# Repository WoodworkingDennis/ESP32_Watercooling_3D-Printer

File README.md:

<h1>ESP32_Watercooling_3D-Printer</h1>
<p>
</br>Ansteuerung von drei unabhängingen PWM-Geräten
</br>Auslesen von sechs verschiedenen PT100 Widerständen
</br>Anzeige und Einstellungen über LCD-Display
</br>ESP32 auf Custom PCB
</p>

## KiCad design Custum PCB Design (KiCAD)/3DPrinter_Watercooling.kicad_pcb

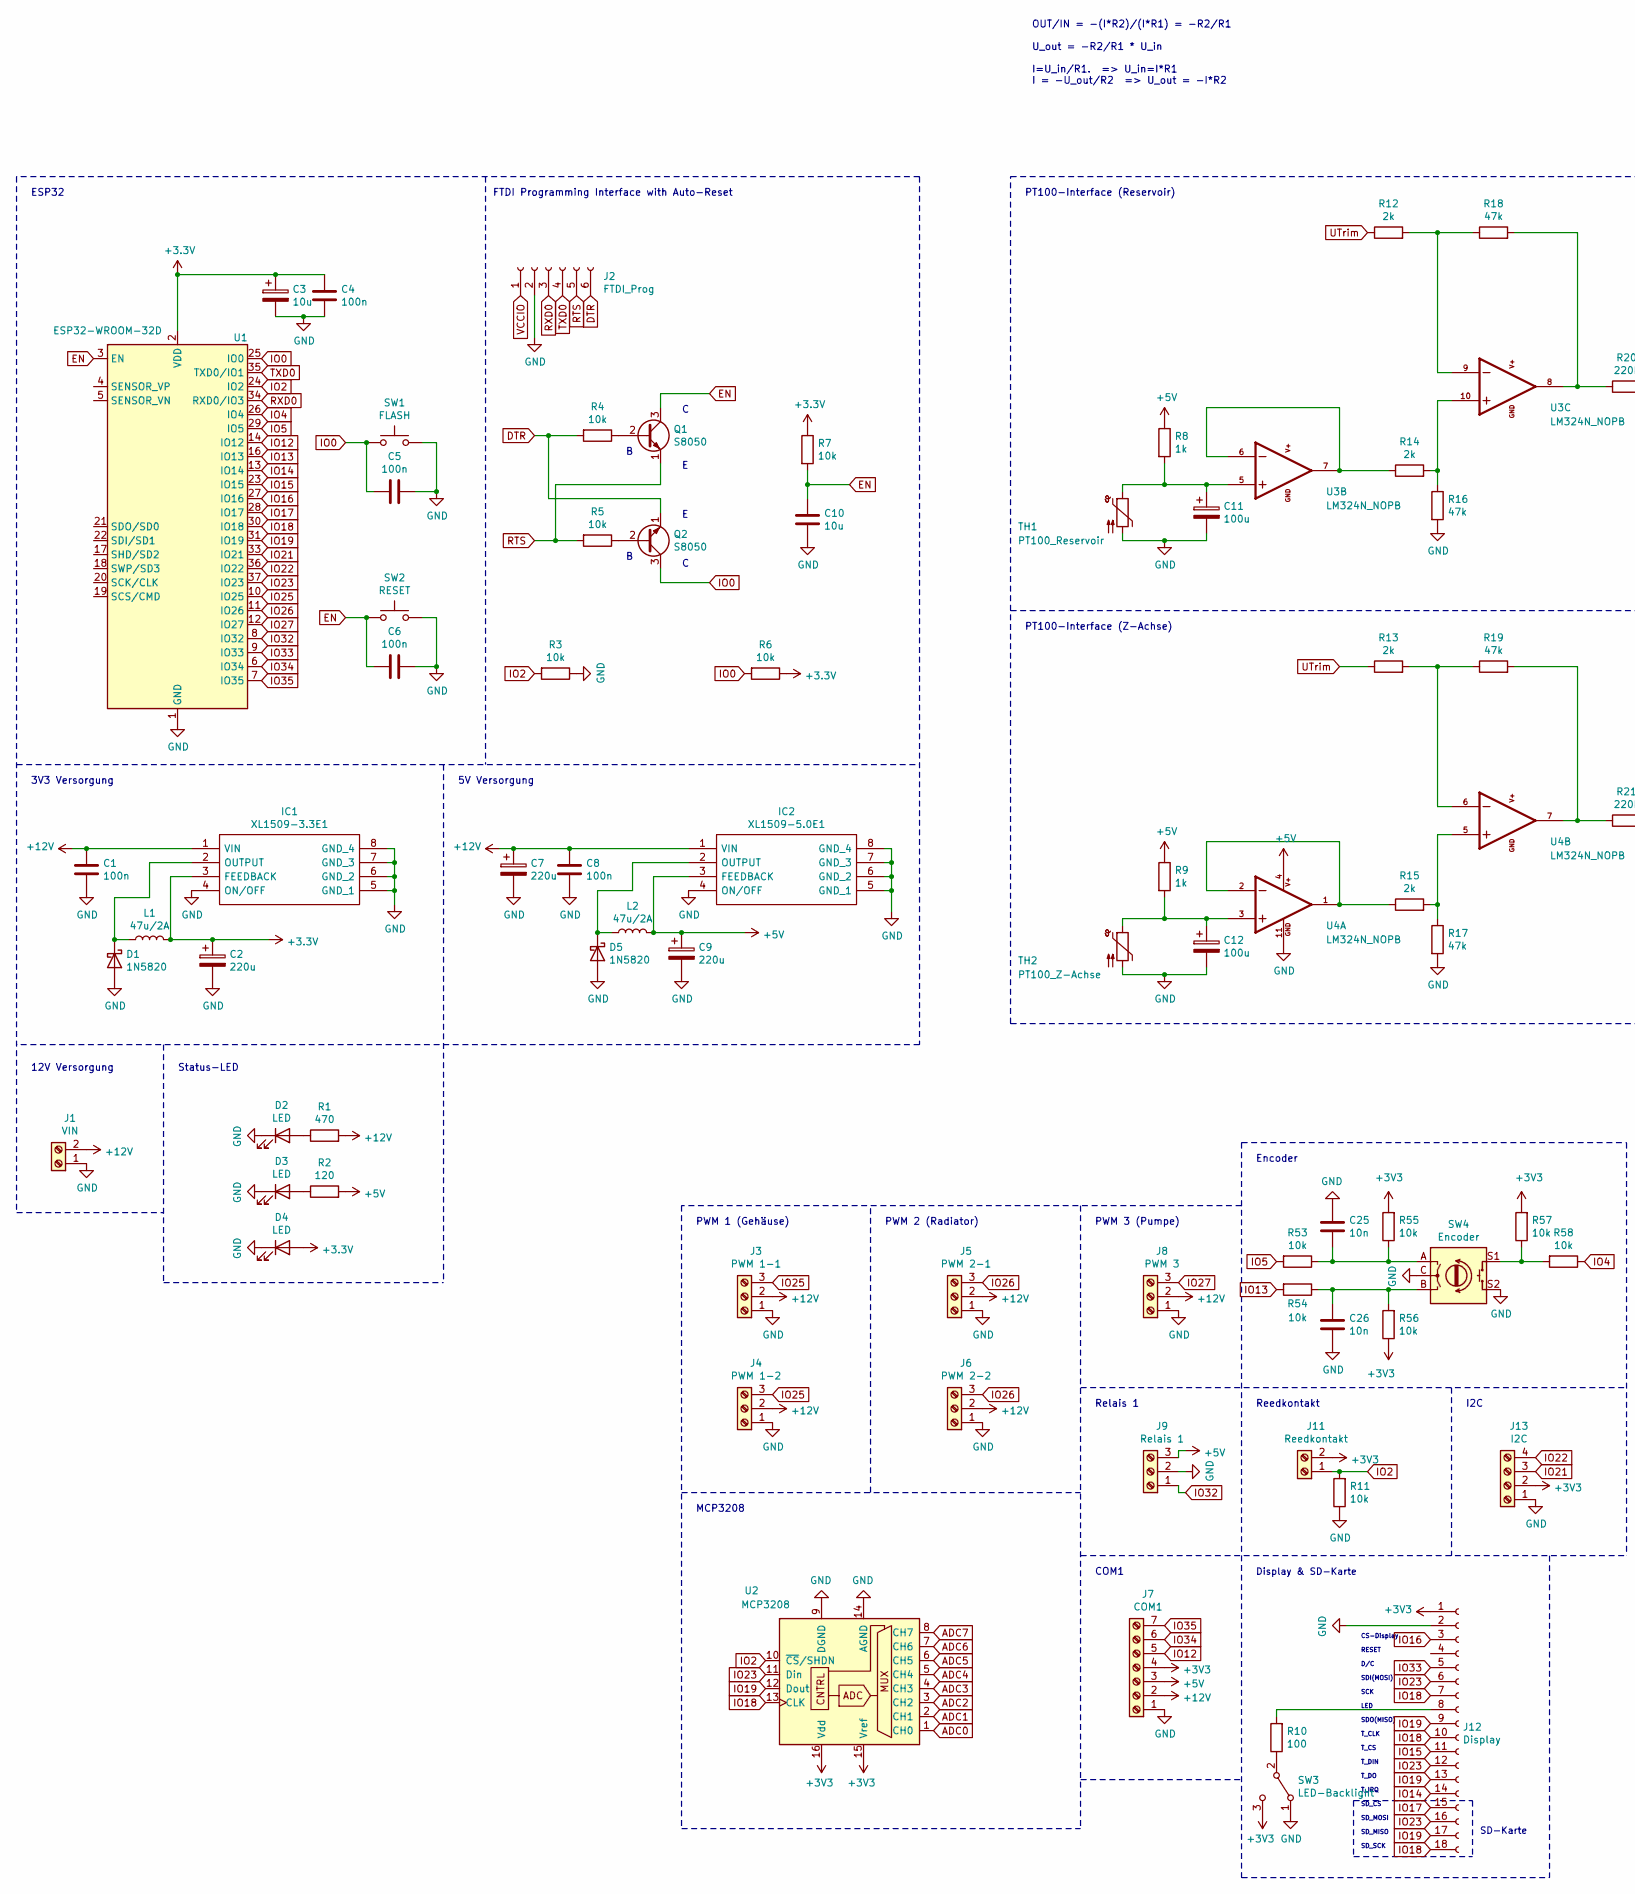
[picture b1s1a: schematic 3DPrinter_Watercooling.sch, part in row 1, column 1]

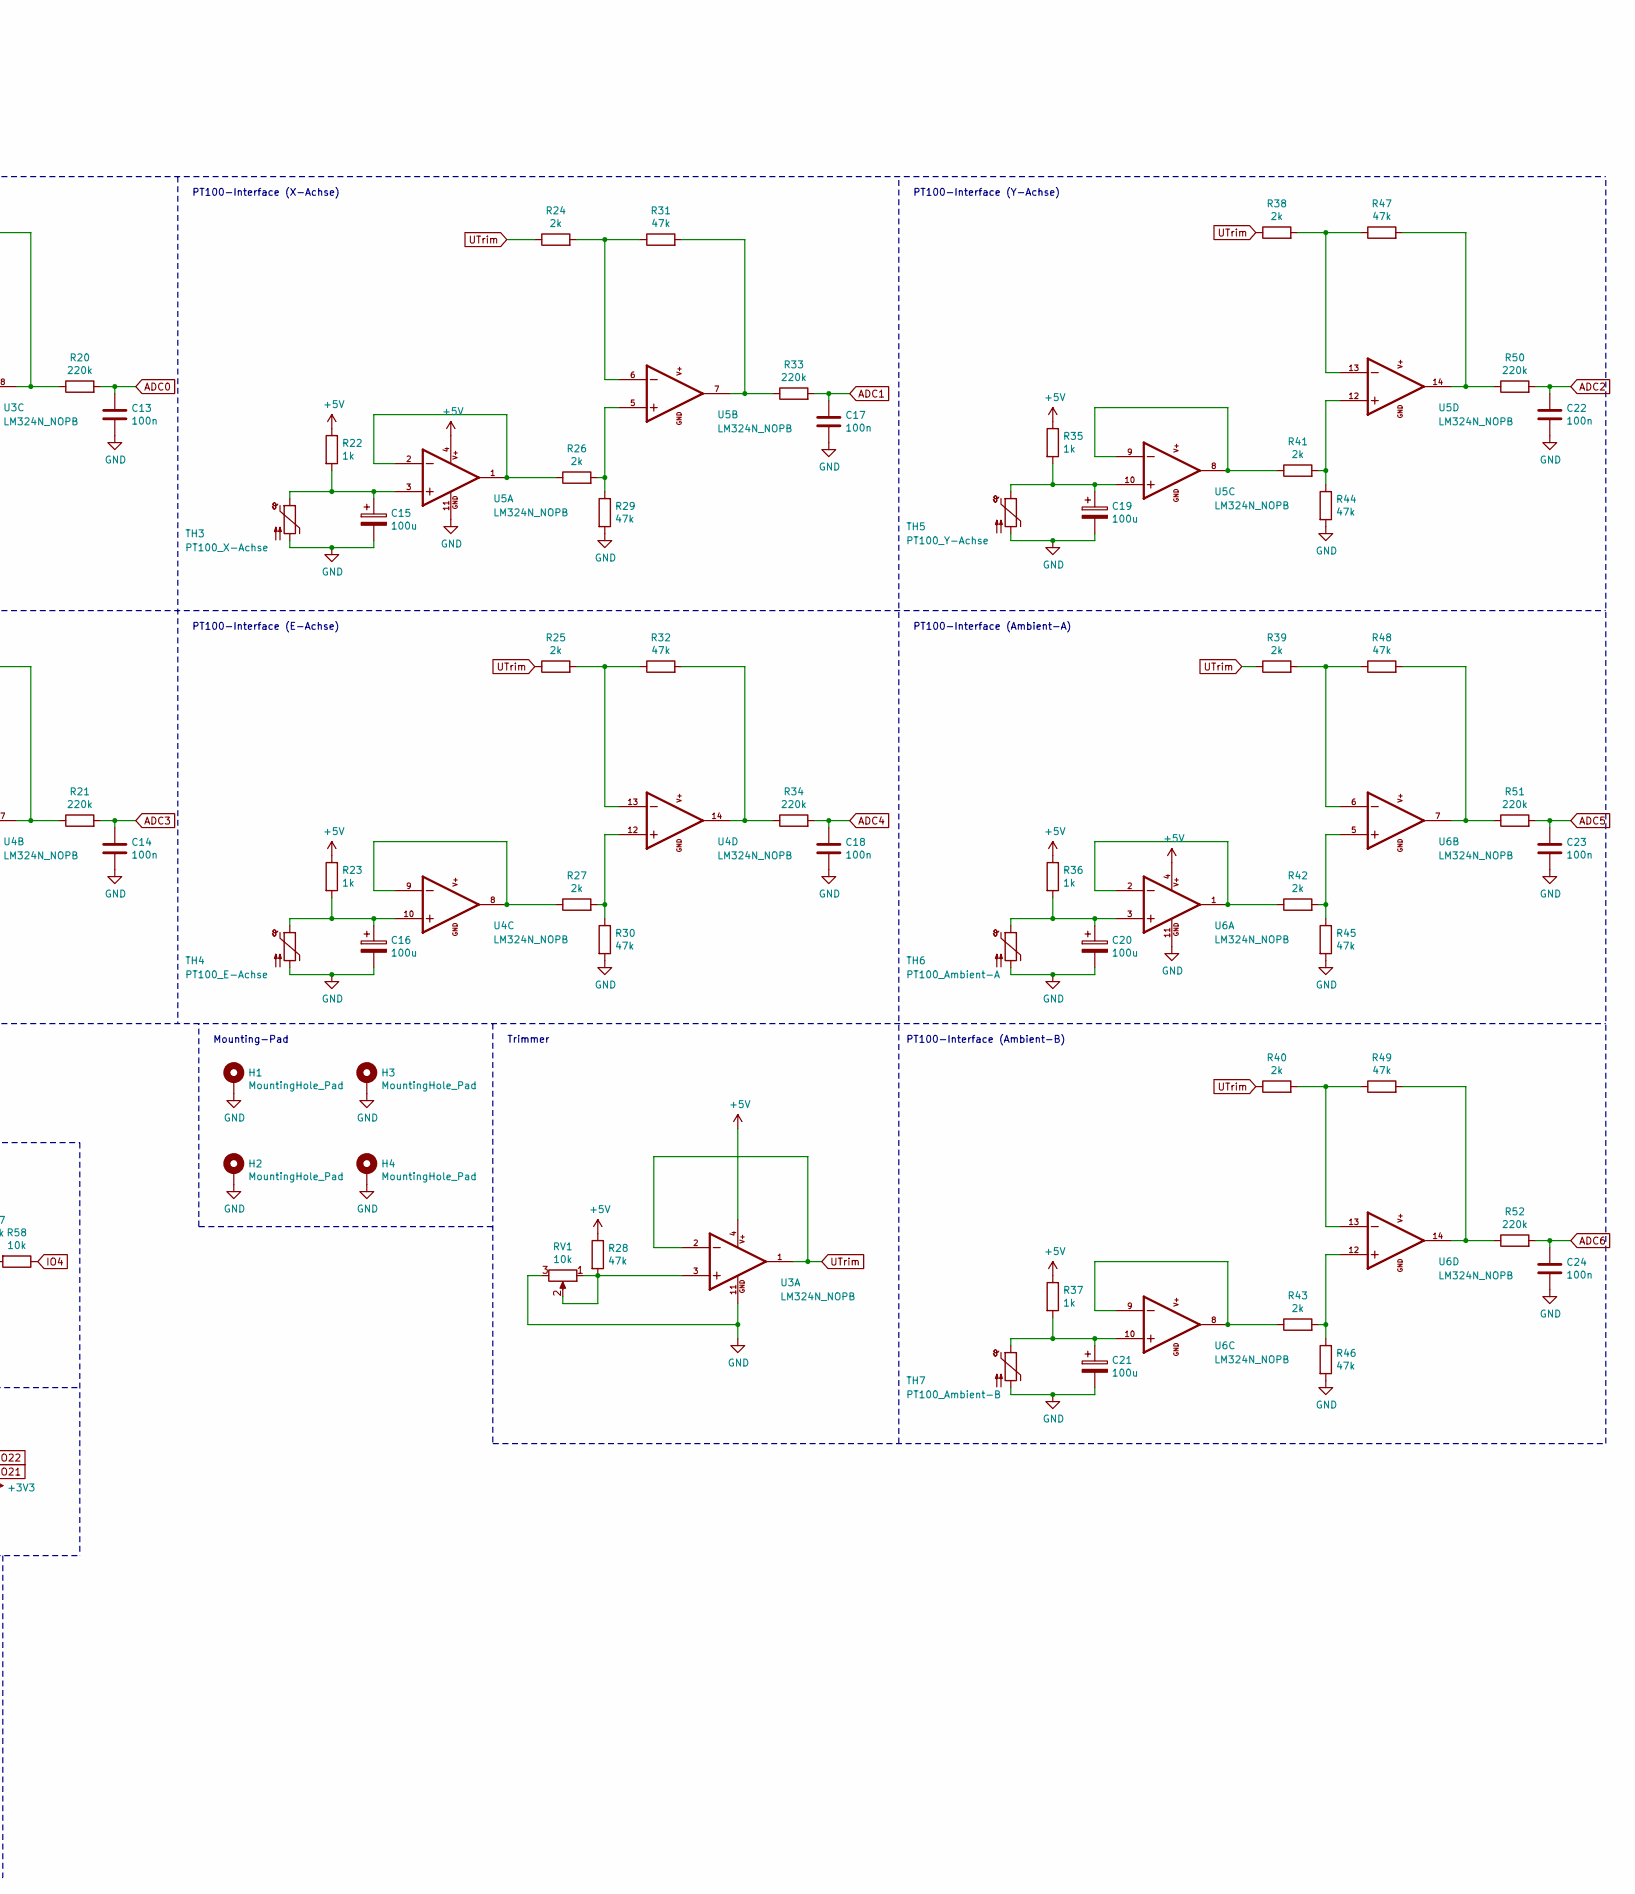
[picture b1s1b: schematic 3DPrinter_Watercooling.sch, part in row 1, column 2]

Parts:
C1, C4, C5, C6, C8, C13, C14, C17, C18, C22, C23, C24: 100n; C_0805_2012Metric_Pad1.18x1.45mm_HandSolder
C2, C7, C9: 220u; CP_Radial_D6.3mm_P2.50mm
C3: 10u; CP_Radial_D4.0mm_P1.50mm
C10: 10u; C_0805_2012Metric_Pad1.18x1.45mm_HandSolder
C11, C12, C15, C16, C19, C20, C21: 100u; CP_Radial_D5.0mm_P2.00mm
C25, C26: 10n; C_0805_2012Metric_Pad1.18x1.45mm_HandSolder
D1, D5: 1N5820; D_DO-201AD_P15.24mm_Horizontal
D2, D3, D4: LED; LED_0805_2012Metric_Pad1.15x1.40mm_HandSolder
H1, H2, H3, H4: MountingHole_Pad; MountingHole_2.2mm_M2_Pad_Via
IC1: XL1509-3.3E1; SOIC127P600X175-8N; Manufacturer_Part_Number XL1509-3.3E1
IC2: XL1509-5.0E1; SOIC127P600X175-8N; Manufacturer_Part_Number XL1509-5.0E1
J1: VIN; WJ301V-5.0-2P
J2: FTDI_Prog; PinHeader_1x06_P2.54mm_Vertical
J3: PWM 1-1; TE_282834-3
J4: PWM 1-2; TE_282834-3
J5: PWM 2-1; TE_282834-3
J6: PWM 2-2; TE_282834-3
J7: COM1; TE_282834-7
J8: PWM 3; TE_282834-3
J9: Relais 1; TE_282834-3
J11: Reedkontakt; TE_282834-2
J12: Display; 3.2 inch 320 240 SPI Serial TFT LCD Module
J13: I2C; TE_282834-4
L1, L2: 47u/2A; L_Radial_D10.0mm_P5.00mm_Fastron_07M
Q1, Q2: S8050; TO-92_Inline
R1: 470; R_Axial_DIN0207_L6.3mm_D2.5mm_P7.62mm_Horizontal
R2: 120; R_Axial_DIN0207_L6.3mm_D2.5mm_P7.62mm_Horizontal
R3, R4, R5, R6, R7, R11, R53, R54, R55, R56, R57, R58: 10k; R_Axial_DIN0207_L6.3mm_D2.5mm_P7.62mm_Horizontal
R8, R9, R22, R23, R35, R36, R37: 1k; R_Axial_DIN0207_L6.3mm_D2.5mm_P7.62mm_Horizontal
R10: 100; R_Axial_DIN0207_L6.3mm_D2.5mm_P7.62mm_Horizontal
R12, R13, R14, R15, R24, R25, R26, R27, R38, R39, R40, R41, R42, R43: 2k; R_Axial_DIN0207_L6.3mm_D2.5mm_P7.62mm_Horizontal
R16, R17, R18, R19, R28, R29, R30, R31, R32, R44, R45, R46, R47, R48, R49: 47k; R_Axial_DIN0207_L6.3mm_D2.5mm_P7.62mm_Horizontal
R20, R21, R33, R34, R50, R51, R52: 220k; R_Axial_DIN0207_L6.3mm_D2.5mm_P7.62mm_Horizontal
RV1: 10k; Potentiometer_Bourns_3296W_Vertical
SW1: FLASH; TS-1187A-B-A-B
SW2: RESET; TS-1187A-B-A-B
SW3: LED-Backlight; SW_Slide_1P2T_CK_OS102011MS2Q
SW4: Encoder; RotaryEncoder_Alps_EC11E-Switch_Vertical_H20mm
TH1: PT100_Reservoir; TE_282834-2
TH2: PT100_Z-Achse; TE_282834-2
TH3: PT100_X-Achse; TE_282834-2
TH4: PT100_E-Achse; TE_282834-2
TH5: PT100_Y-Achse; TE_282834-2
TH6: PT100_Ambient-A; TE_282834-2
TH7: PT100_Ambient-B; TE_282834-2
U1: ESP32-WROOM-32D; ESP32-WROOM-32
U2: MCP3208; SOIC127P600X175-16N
U3, U4, U5, U6: LM324N_NOPB; SOIC-14_3.9x8.7mm_P1.27mm; PARTREV D

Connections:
+5V: C9.1, IC2.3 (FEEDBACK), J7.3, J9.3, L2.2, R2.2, R8.1, R9.1, R22.1, R23.1, R28.1, R35.1, R36.1, R37.1, U3.4, U4.4, U5.4, U6.4
+12V: C1.1, C7.1, C8.1, IC1.1 (VIN), IC2.1 (VIN), J1.2, J3.2, J4.2, J5.2, J6.2, J7.2, J8.2, R1.2
ADC0: C13.1, R20.2, U2.1 (CH0)
ADC1: C17.1, R33.2, U2.2 (CH1)
ADC2: C22.1, R50.2, U2.3 (CH2)
ADC3: C14.1, R21.2, U2.4 (CH3)
ADC4: C18.1, R34.2, U2.5 (CH4)
ADC5: C23.1, R51.2, U2.6 (CH5)
ADC6: C24.1, R52.2, U2.7 (CH6)
ADC7: U2.8 (CH7)
DTR: J2.6, Q2.1 (E), R4.2
EN: C6.2, C10.1, Q1.3 (C), R7.2, SW2.1, U1.3 (EN)
GND: C1.2, C2.2, C3.2, C4.2, C5.1, C6.1, C7.2, C8.2, C9.2, C10.2, C11.2, C12.2, C13.2, C14.2, C15.2, C16.2, C17.2, C18.2, C19.2, C20.2, C21.2, C22.2, C23.2, C24.2, C25.1, C26.2, D1.2 (A), D2.1 (K), D3.1 (K), D4.1 (K), D5.2 (A), H1.1, H2.1, H3.1, H4.1, IC1.4 (ON/OFF), IC1.5 (GND_1), IC1.6 (GND_2), IC1.7 (GND_3), IC1.8 (GND_4), IC2.4 (ON/OFF), IC2.5 (GND_1), IC2.6 (GND_2), IC2.7 (GND_3), IC2.8 (GND_4), J1.1, J2.2, J3.1, J4.1, J5.1, J6.1, J7.1, J8.1, J9.2, J12.2, J13.1, R3.1, R11.1, R16.2, R17.2, R29.2, R30.2, R44.2, R45.2, R46.2, RV1.3, SW1.2, SW2.2, SW3.1 (A), SW4.C, SW4.S2, TH1.2, TH2.2, TH3.2, TH4.2, TH5.2, TH6.2, TH7.2, U1.1 (GND), U1.15 (GND), U1.38 (GND), U1.39 (GND), U2.9 (DGND), U2.14 (AGND), U3.11, U4.11, U5.11, U6.11
IO0: C5.2, Q2.3 (C), R6.2, SW1.1, U1.25 (IO0)
IO2: J11.1, R3.2, R11.2, U1.24 (IO2), U2.10 (~CS~/SHDN)
IO4: R58.1, U1.26 (IO4)
IO5: R53.2, U1.29 (IO5)
IO12: J7.5, U1.14 (IO12)
IO13: R54.2, U1.16 (IO13)
IO14: J12.14, U1.13 (IO14)
IO15: J12.11, U1.23 (IO15)
IO16: J12.3, U1.27 (IO16)
IO17: J12.15, U1.28 (IO17)
IO18: J12.7, J12.10, J12.18, U1.30 (IO18), U2.13 (CLK)
IO19: J12.9, J12.13, J12.17, U1.31 (IO19), U2.12 (Dout)
IO21: J13.3, U1.33 (IO21)
IO22: J13.4, U1.36 (IO22)
IO23: J12.6, J12.12, J12.16, U1.37 (IO23), U2.11 (Din)
IO25: J3.3, J4.3, U1.10 (IO25)
IO26: J5.3, J6.3, U1.11 (IO26)
IO27: J8.3, U1.12 (IO27)
IO32: J9.1, U1.8 (IO32)
IO33: J12.5, U1.9 (IO33)
IO34: J7.6, U1.6 (IO34)
IO35: J7.7, U1.7 (IO35)
unnamed: C11.1, R8.2, TH1.1, U3.5
unnamed: C12.1, R9.2, TH2.1, U4.3
unnamed: C15.1, R22.2, TH3.1, U5.3
unnamed: C16.1, R23.2, TH4.1, U4.10
unnamed: C19.1, R35.2, TH5.1, U5.10
unnamed: C20.1, R36.2, TH6.1, U6.3
unnamed: C21.1, R37.2, TH7.1, U6.10
unnamed: C25.2, R53.1, R55.1, SW4.A
unnamed: C26.1, R54.1, R56.2, SW4.B
unnamed: D1.1 (K), IC1.2 (OUTPUT), L1.1
unnamed: D2.2 (A), R1.1
unnamed: D3.2 (A), R2.1
unnamed: D5.1 (K), IC2.2 (OUTPUT), L2.1
unnamed: J12.8, R10.2
unnamed: Q1.2 (B), R4.1
unnamed: Q2.2 (B), R5.1
unnamed: R10.1, SW3.2 (B)
unnamed: R12.2, R18.1, U3.9
unnamed: R13.2, R19.1, U4.6
unnamed: R14.1, U3.6, U3.7
unnamed: R14.2, R16.1, U3.10
unnamed: R15.1, U4.1, U4.2
unnamed: R15.2, R17.1, U4.5
unnamed: R18.2, R20.1, U3.8
unnamed: R19.2, R21.1, U4.7
unnamed: R24.2, R31.1, U5.6
unnamed: R25.2, R32.1, U4.13
unnamed: R26.1, U5.1, U5.2
unnamed: R26.2, R29.1, U5.5
unnamed: R27.1, U4.8, U4.9
unnamed: R27.2, R30.1, U4.12
unnamed: R28.2, RV1.1, RV1.2, U3.3
unnamed: R31.2, R33.1, U5.7
unnamed: R32.2, R34.1, U4.14
unnamed: R38.2, R47.1, U5.13
unnamed: R39.2, R48.1, U6.6
unnamed: R40.2, R49.1, U6.13
unnamed: R41.1, U5.8, U5.9
unnamed: R41.2, R44.1, U5.12
unnamed: R42.1, U6.1, U6.2
unnamed: R42.2, R45.1, U6.5
unnamed: R43.1, U6.8, U6.9
unnamed: R43.2, R46.1, U6.12
unnamed: R47.2, R50.1, U5.14
unnamed: R48.2, R51.1, U6.7
unnamed: R49.2, R52.1, U6.14
unnamed: R57.1, R58.2, SW4.S1
RTS: J2.5, Q1.1 (E), R5.2
RXD0: J2.3, U1.34 (RXD0/IO3)
TXD0: J2.4, U1.35 (TXD0/IO1)
UTrim: R12.1, R13.1, R24.1, R25.1, R38.1, R39.1, R40.1, U3.1, U3.2
VCCIO: J2.1

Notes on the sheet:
ESP32
FTDI Programming Interface with Auto-Reset
PT100-Interface (Reservoir)
Mounting-Pad
PT100-Interface (X-Achse)
PT100-Interface (Y-Achse)
PT100-Interface (Z-Achse)
PT100-Interface (Ambient-A)
PT100-Interface (Ambient-B)
Display & SD-Karte
SD-Karte
SD_SCK
SD_MISO
SD_MOSI
SD_CS
T_IRQ
T_DO
T_DIN
T_CS
T_CLK
SDO(MISO)
LED
SCK
SDI(MOSI)
D/C
RESET
CS-Display
COM1
MCP3208
Reedkontakt
Relais 1
Encoder
PWM 3 (Pumpe)
PWM 2 (Radiator)
PWM 1 (Gehäuse)
3V3 Versorgung
12V Versorgung
OUT/IN = -(I*R2)/(I*R1) = -R2/R1 U_out = -R2/R1 * U_in I=U_in/R1. => U_in=I*R1 I = -U_out/R2 => U_out = -I*R2
Trimmer
PT100-Interface (E-Achse)

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
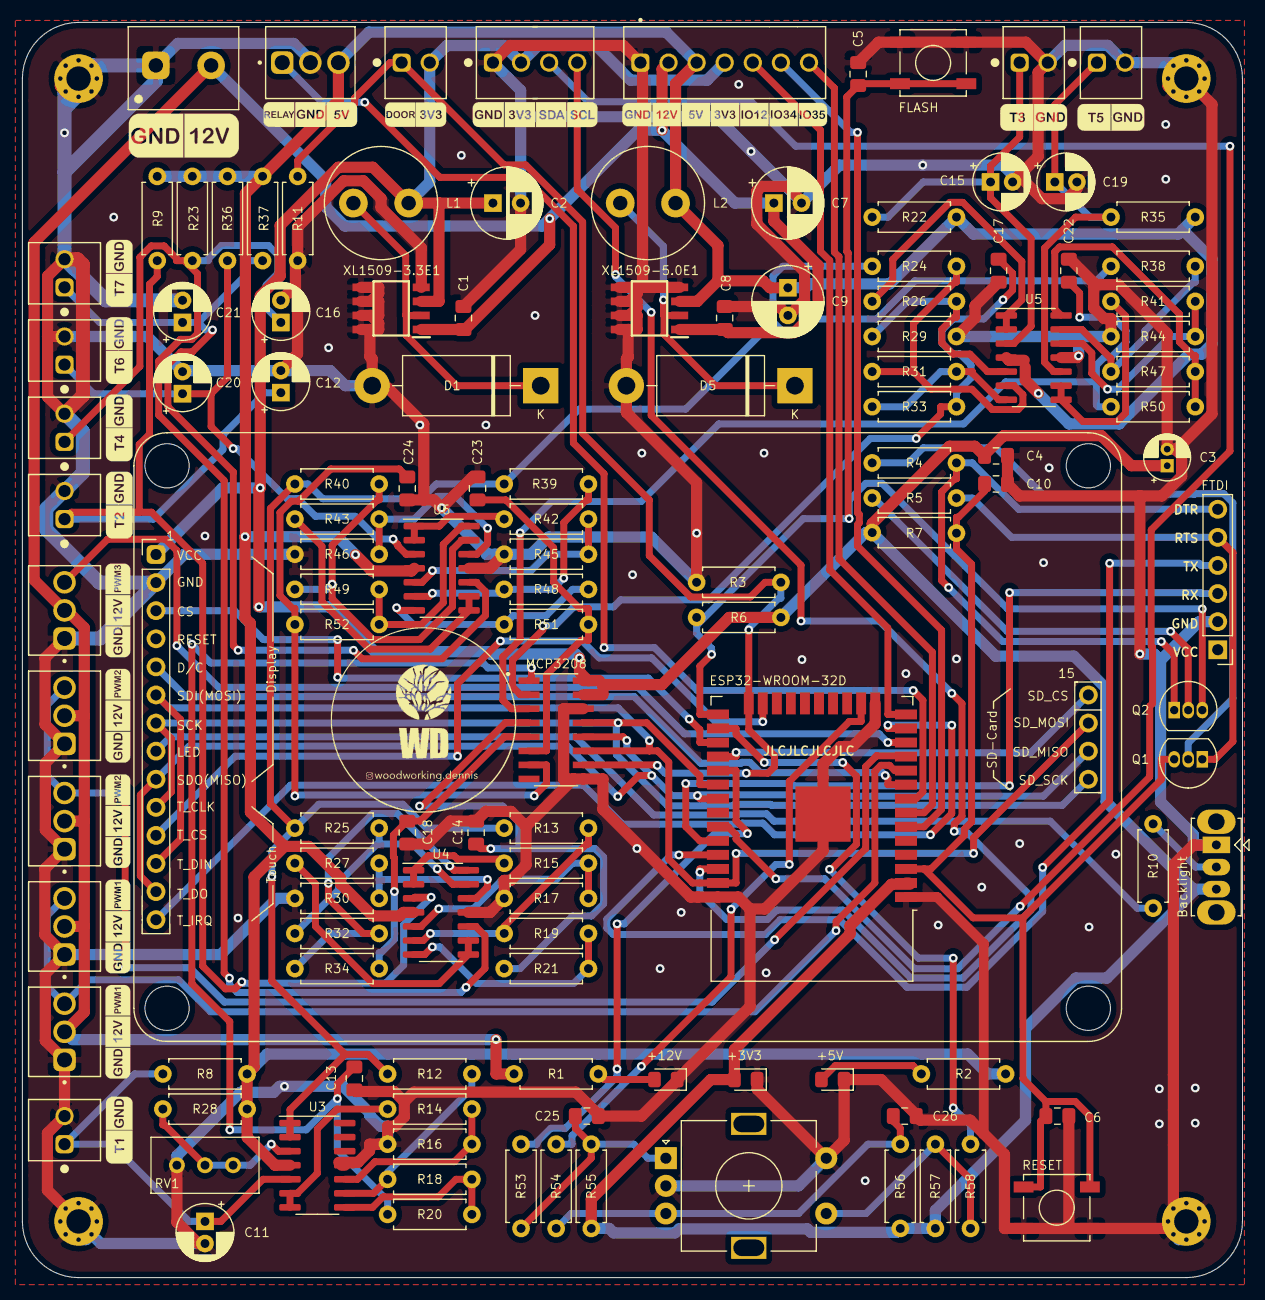
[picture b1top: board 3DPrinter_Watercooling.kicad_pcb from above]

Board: 2 copper layers, 110.3 x 113.5 mm, 146 parts (0 on the bottom side), 86 nets.

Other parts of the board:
G1: LOGO; T5-GND_6x2.4 mm
G2: LOGO; T3-GND_6x2.4 mm
G3: LOGO; COM1
G4: LOGO; I2C
G5: LOGO; DOOR-3V3
G6: LOGO; Relay-GND-5V
G7: LOGO; 12V-GND_10x4 mm
G8: LOGO; T7-GND_6x2.4 mm
G9: LOGO; T6-GND_6x2.4 mm
G10: LOGO; T4-GND_6x2.4 mm
G11: LOGO; T2-GND_6x2.4 mm
G12: LOGO; GND-12V-PWM3
G13, G14: LOGO; GND-12V-PWM2
G15, G16: LOGO; GND-12V-PWM1
G17: LOGO; T1-GND_6x2.4 mm
